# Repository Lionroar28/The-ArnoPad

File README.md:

# The-ArnoPad

It is a hackpad that can change the volume(rotary dial), has 6 buttons that can do whatever you want it to, a screen for your favourite gifs and leds for nessacery lighting

The features of the Arno pad are:
<p>A cool case that has a window to show spiderman and orpheus</p>
<p>A screen</p>
<p>A rotary encoder to increase and decraese volume</p>
<p>6 leds for switch backlighting</p>
<p>6 keys</p>

CAD medel case:
The case has 4 holes to put everything together
It is made in 2 pieces, the case and the lid
It also has a little hole to show spiderman and orpheus on the PCB
An embossing of the word ArnoPad on the side to show what it is
I made it in Fusion360
                                                                 
The PCB:
Here is the PCB I made, I made it in KiCad.

PCB

Schematic

BOM:
<p>6x Cherry mx switches</p>
<p>6x keycaps</p>
<p>4x screws</p>
<p>4x bolts</p>
<p>6x diodes</p>
<p>6x LED's</p>
<p>1x OLED display</p>
<p>1x rotary dial</p>
<p>1x XIAO controller</p>
<p>1x 3d printed case</p>
<p>1x custom ArnoPad PCB</p>

Firmware:
I have not made the firmware yet

(made for stardance)

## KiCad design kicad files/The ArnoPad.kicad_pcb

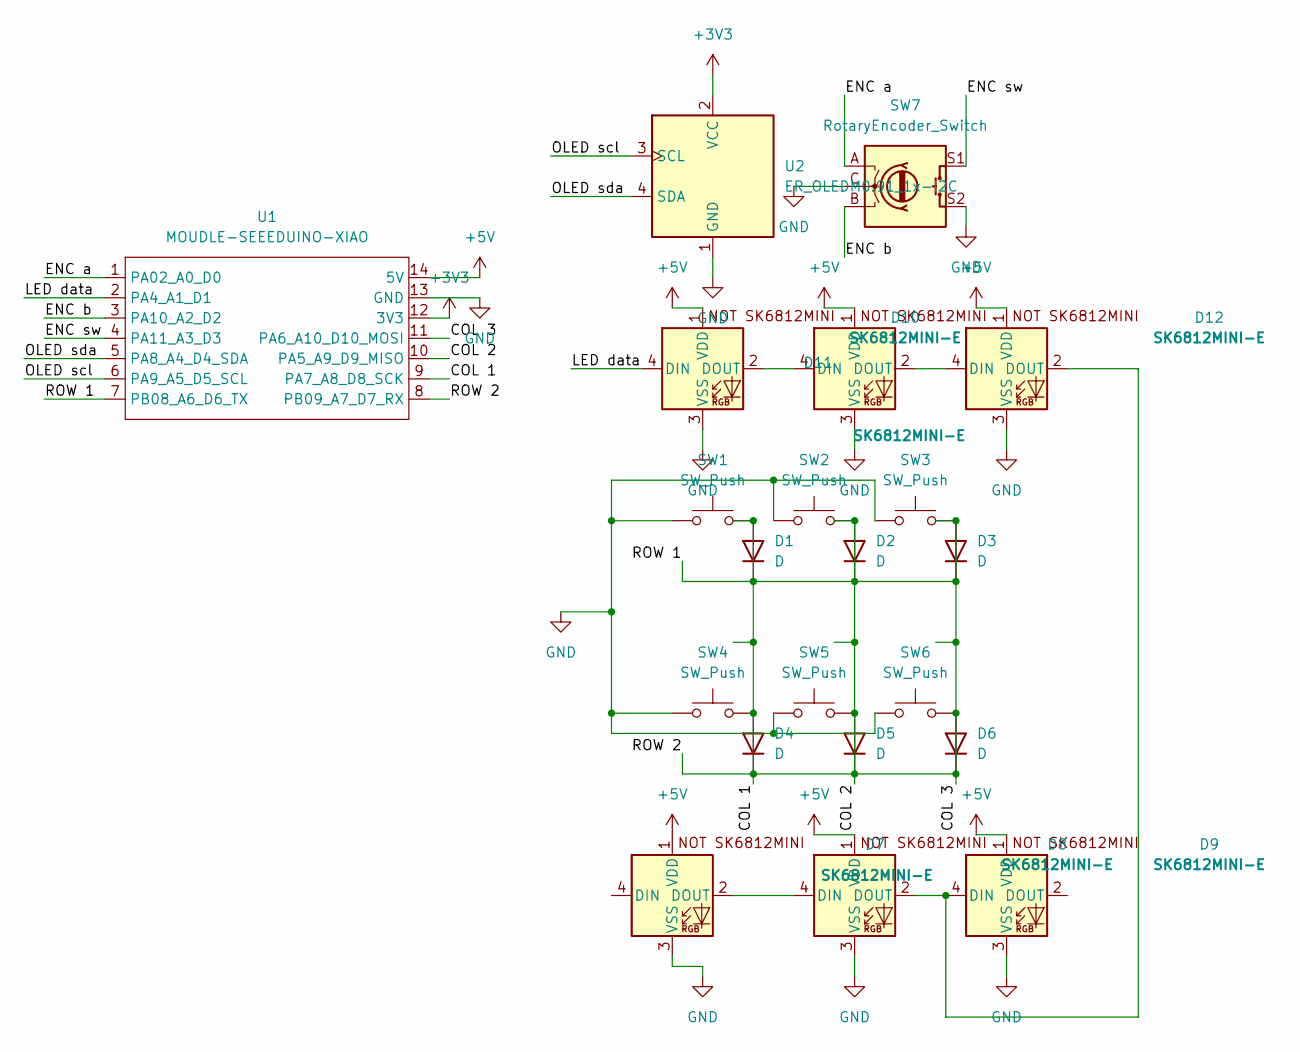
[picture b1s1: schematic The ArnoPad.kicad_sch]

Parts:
D1, D2, D3, D4, D5, D6: D; D_DO-35_SOD27_P7.62mm_Horizontal
D7, D8, D9, D10, D11, D12: SK6812MINI-E; LED_SK6812MINI-E_3.2x2.8mm_P1.5mm_ReverseMount
SW1, SW2, SW3, SW4, SW5, SW6: SW_Push; SW_Cherry_MX_1.00u_PCB
SW7: RotaryEncoder_Switch; RotaryEncoder_Alps_EC11E-Switch_Vertical_H20mm
U1: MOUDLE-SEEEDUINO-XIAO; XIAO-Generic-Hybrid-14P-2.54-21X17.8MM
U2: ER_OLEDM0.91_1x-I2C

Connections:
+3V3: U1.12 (3V3), U2.2 (VCC)
+5V: D7.1 (VDD), D8.1 (VDD), D9.1 (VDD), D10.1 (VDD), D11.1 (VDD), D12.1 (VDD), U1.14 (5V)
/COL 1: D1.1 (K), D1.2 (A), D2.1 (K), D2.2 (A), D3.1 (K), D3.2 (A), D4.1 (K), D4.2 (A), D5.1 (K), D5.2 (A), D6.1 (K), D6.2 (A), SW1.2, SW2.2, SW3.2, SW4.2, SW5.2, SW6.2, U1.7 (PB08_A6_D6_TX), U1.8 (PB09_A7_D7_RX), U1.9 (PA7_A8_D8_SCK), U1.10 (PA5_A9_D9_MISO), U1.11 (PA6_A10_D10_MOSI)
/ENC a: SW7.A, U1.1 (PA02_A0_D0)
/ENC b: SW7.B, U1.3 (PA10_A2_D2)
/ENC sw: SW7.S1, U1.4 (PA11_A3_D3)
/LED data: D10.4 (DIN), U1.2 (PA4_A1_D1)
/OLED scl: U1.6 (PA9_A5_D5_SCL), U2.3 (SCL)
/OLED sda: U1.5 (PA8_A4_D4_SDA), U2.4 (SDA)
GND: D7.3 (VSS), D8.3 (VSS), D9.3 (VSS), D10.3 (VSS), D11.3 (VSS), D12.3 (VSS), SW1.1, SW2.1, SW3.1, SW4.1, SW5.1, SW6.1, SW7.C, SW7.S2, U1.13 (GND), U2.1 (GND)
unnamed: D7.2 (DOUT), D8.4 (DIN)
unnamed: D10.2 (DOUT), D11.4 (DIN)
unnamed: D11.2 (DOUT), D12.4 (DIN)
unnamed: D8.2 (DOUT), D9.4 (DIN), D12.2 (DOUT)

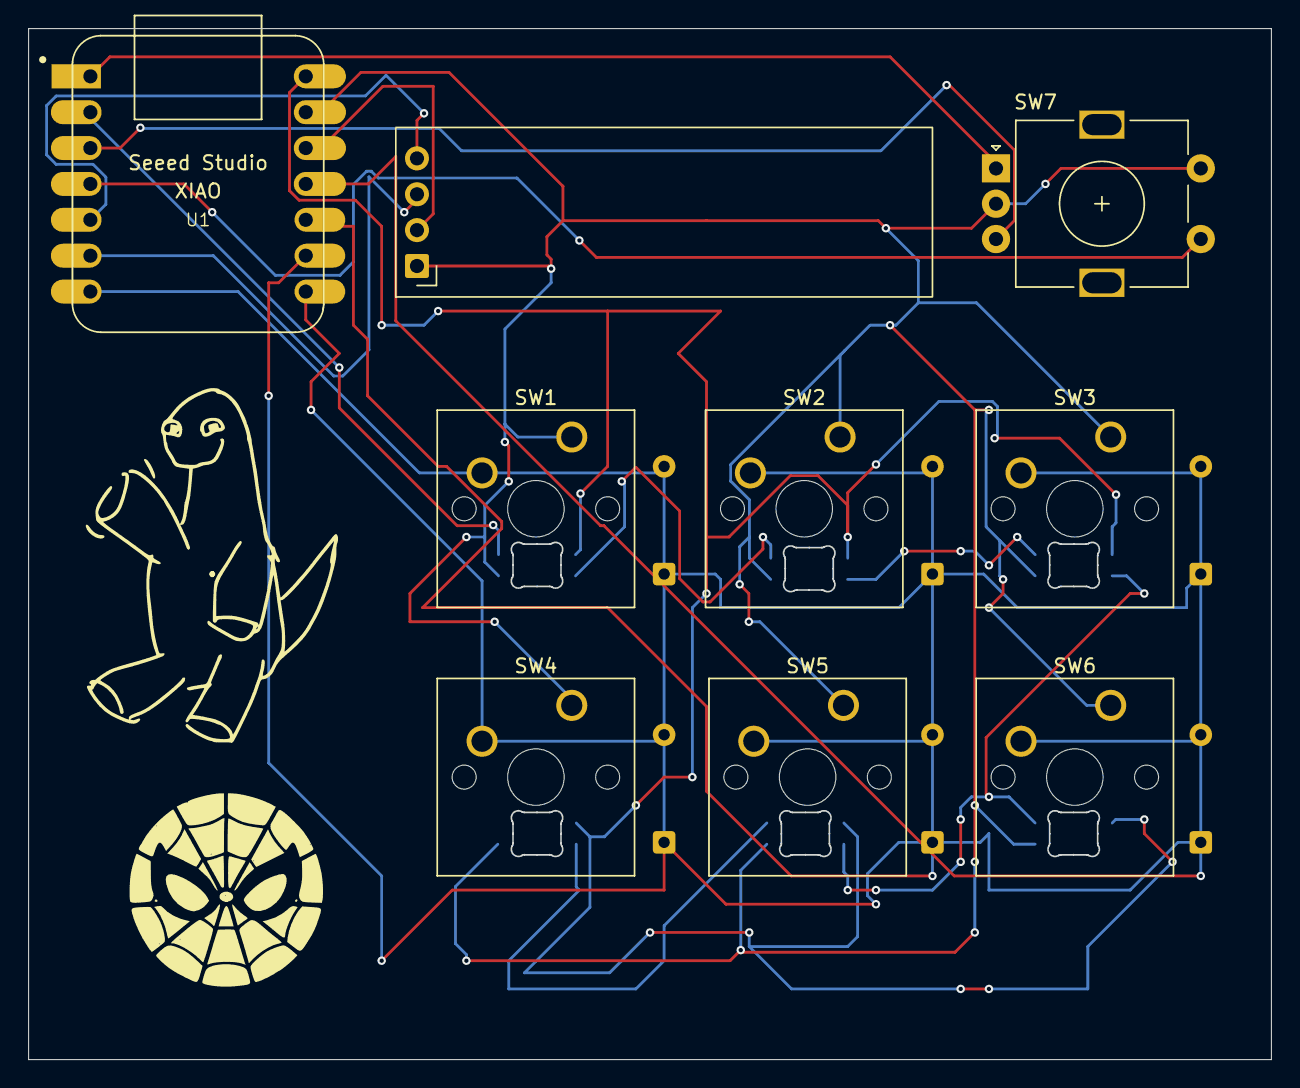
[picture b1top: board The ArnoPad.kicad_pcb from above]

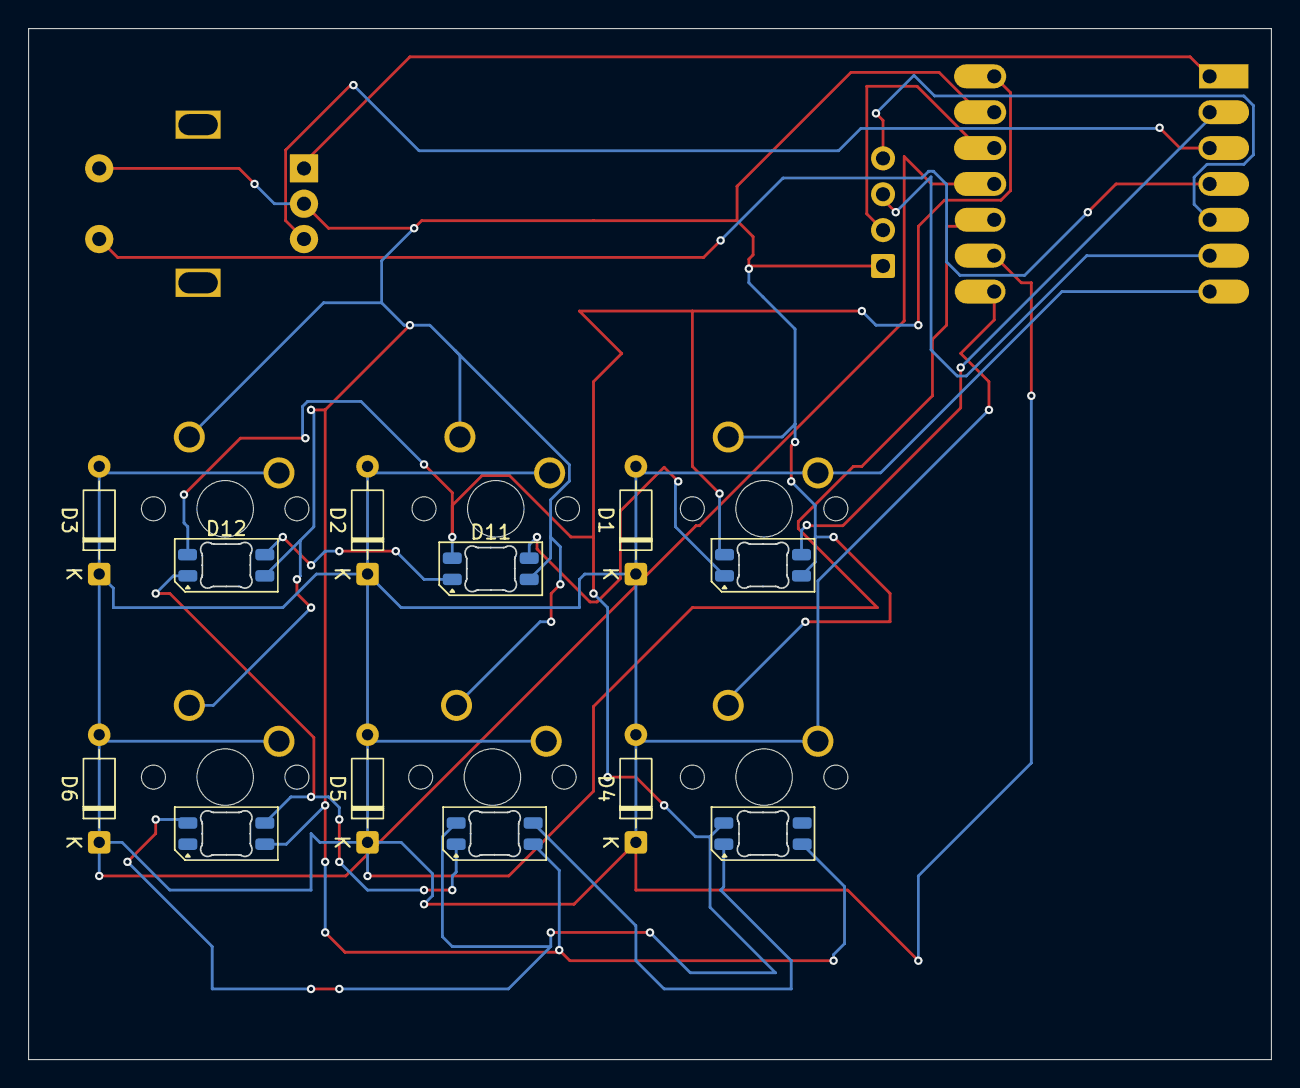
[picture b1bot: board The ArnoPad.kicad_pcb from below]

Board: 2 copper layers, 88.0 x 73.0 mm, 23 parts (12 on the bottom side), 14 nets.

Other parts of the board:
 .: LOGO
.: LOGO
